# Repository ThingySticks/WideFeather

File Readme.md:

# Wide Feater Wing ThingyStick Prototype PCB

Wide format prototype board for Feather based boards..

## V1

### Features:

* USB power in via A Connector on right hand edge.
* LED/Resistor/Capacitor 1206 pads along top edge, along both top and bottom or board (although you probably don't want both at once!)
* 4 mounting holes (M3 machine screw) to allow board to be mounted in case for final use.
* PCB 100mm x 50mm. Holes at 4mm from edge.

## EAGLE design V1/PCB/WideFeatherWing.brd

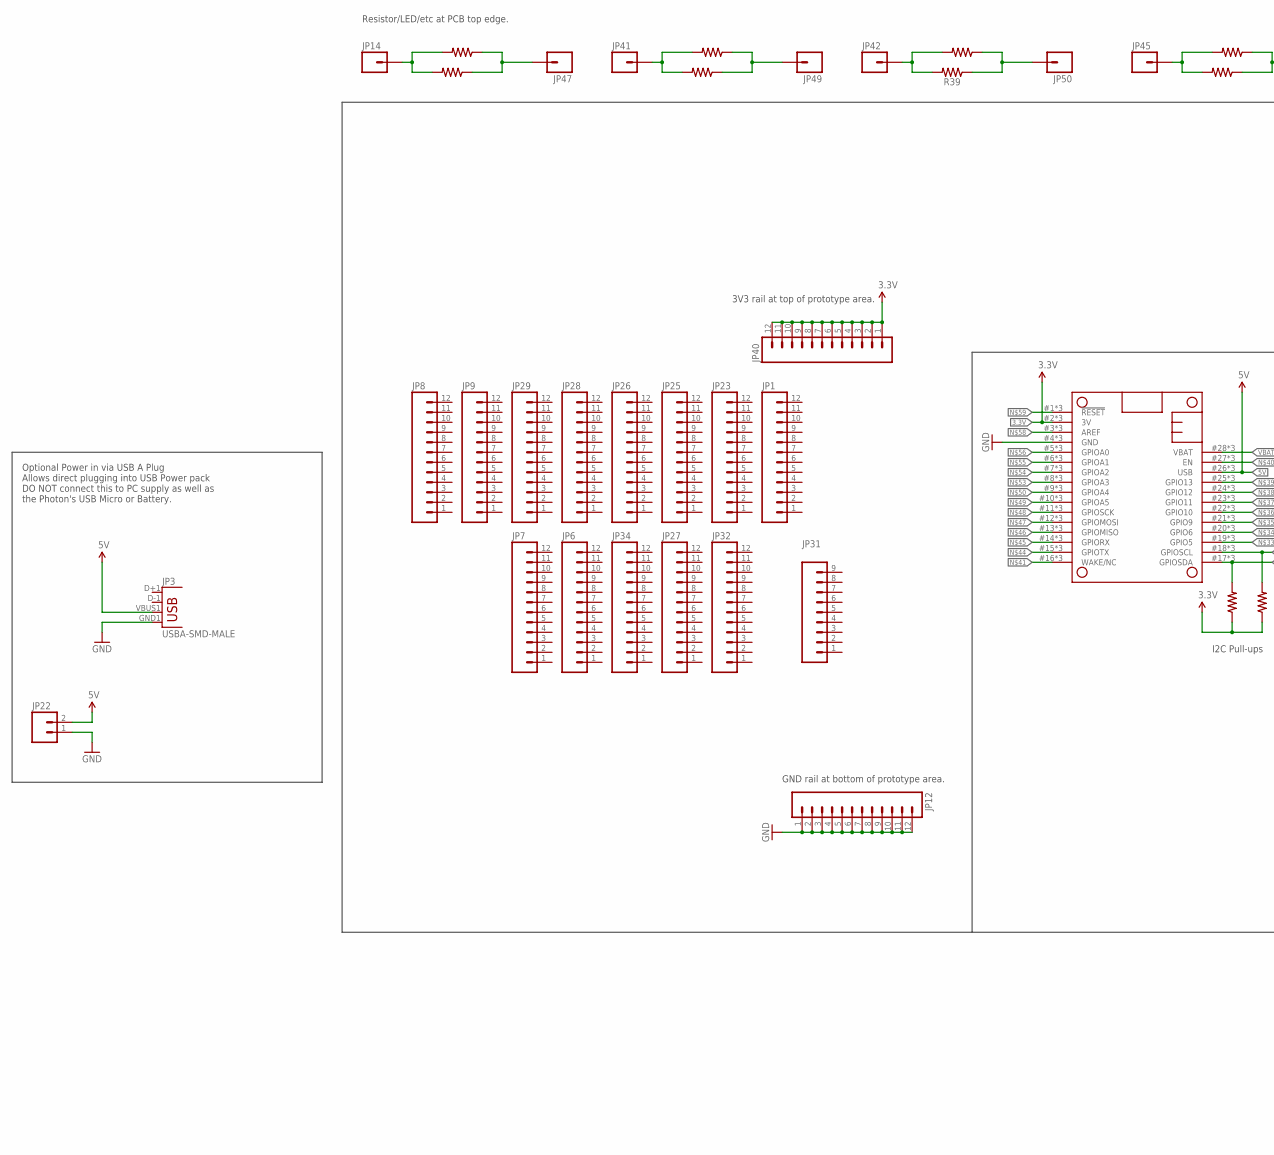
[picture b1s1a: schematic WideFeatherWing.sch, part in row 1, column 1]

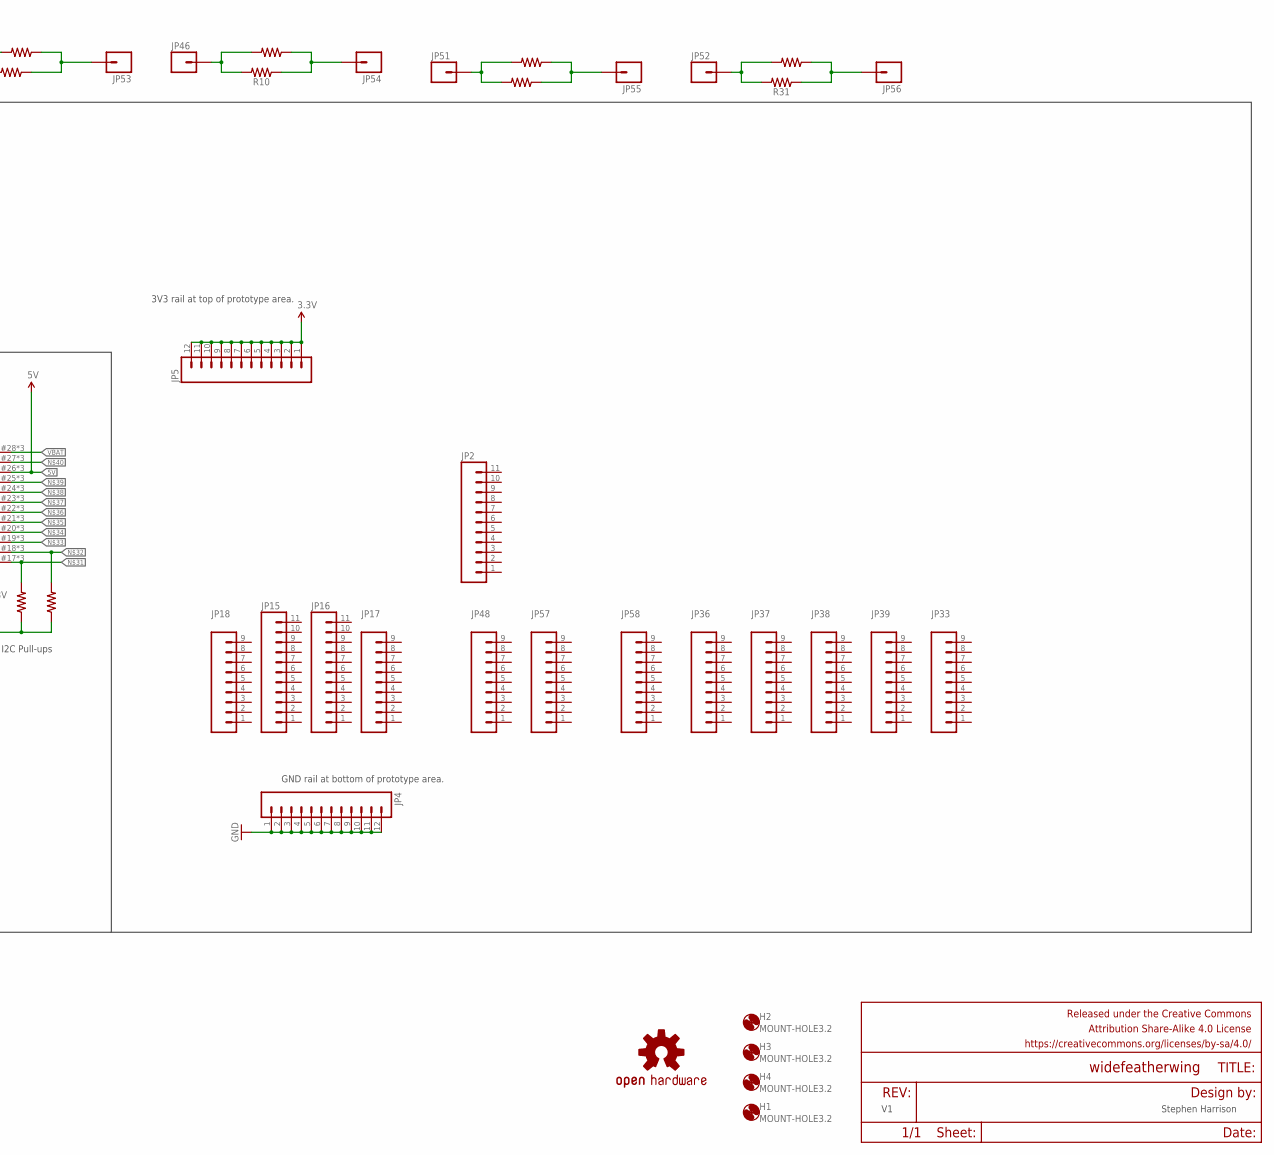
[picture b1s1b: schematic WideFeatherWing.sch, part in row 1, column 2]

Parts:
FRAME1: FRAME-LEDGER; CREATIVE_COMMONS
H1, H2, H3, H4: MOUNT-HOLE3.2; 3,2
JP1, JP6, JP7, JP8, JP9, JP23, JP25, JP26, JP27, JP28, JP29, JP32, JP34: M12NO_SILK; 1X12_NO_SILK
JP2, JP15, JP16: M111X11_NO_SILK; 1X11_NO_SILK
JP3: USBA-SMD-MALE; USB-A-SMT-MALE
JP4, JP5, JP12, JP40: M12PTH; 1X12
JP14, JP41, JP42, JP45, JP46, JP47, JP49, JP50, JP51, JP52, JP53, JP54, JP55, JP56: M01PTH; 1X01
JP17, JP18, JP31, JP33, JP36, JP37, JP38, JP39, JP48, JP57, JP58: M09NO_SILK; 1X09_NO_SILK
JP22: M021X02_NO_SILK; 1X02_NO_SILK
LOGO1: OSHW-LOGOM; OSHW-LOGO-M
MS1: FEATHERWINGFEATHEWING_BREAKOUT; FEATHERWING_BREAKOUT
R5, R9, R10, R17, R24, R30, R31, R32, R34, R35, R36, R37, R39, R40, R41, R44: 1206

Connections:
3.3V: JP5.1, JP5.2, JP5.3, JP5.4, JP5.5, JP5.6, JP5.7, JP5.8, JP5.9, JP5.10, JP5.11, JP5.12, JP40.1, JP40.2, JP40.3, JP40.4, JP40.5, JP40.6, JP40.7, JP40.8, JP40.9, JP40.10, JP40.11, JP40.12, MS1.2 (3V), MS1.#2 (3V), MS1.@2 (3V), R5.1, R9.1
5V: JP3.VBUS1 (VBUS), JP22.2, MS1.26 (USB), MS1.#26 (USB), MS1.@26 (USB)
GND: JP3.GND1 (GND), JP4.1, JP4.2, JP4.3, JP4.4, JP4.5, JP4.6, JP4.7, JP4.8, JP4.9, JP4.10, JP4.11, JP4.12, JP12.1, JP12.2, JP12.3, JP12.4, JP12.5, JP12.6, JP12.7, JP12.8, JP12.9, JP12.10, JP12.11, JP12.12, JP22.1, MS1.4 (GND), MS1.#4 (GND), MS1.@4 (GND)
unnamed: JP42.1, R39.2, R44.2
unnamed: JP53.1, R17.1, R24.1
unnamed: JP45.1, R17.2, R24.2
unnamed: JP46.1, R10.2, R30.2
unnamed: JP54.1, R10.1, R30.1
unnamed: JP55.1, R32.1, R36.1
unnamed: JP51.1, R32.2, R36.2
unnamed: JP56.1, R31.1, R37.1
unnamed: JP52.1, R31.2, R37.2
unnamed: MS1.17 (GPIOSDA), MS1.#17 (GPIOSDA), MS1.@17 (GPIOSDA), R5.2
unnamed: MS1.18 (GPIOSCL), MS1.#18 (GPIOSCL), MS1.@!8 (GPIOSCL), R9.2
unnamed: MS1.19 (GPIO5), MS1.#19 (GPIO5), MS1.@19 (GPIO5)
unnamed: MS1.20 (GPIO6), MS1.#20 (GPIO6), MS1.@20 (GPIO6)
unnamed: MS1.21 (GPIO9), MS1.#21 (GPIO9), MS1.@21 (GPIO9)
unnamed: MS1.22 (GPIO10), MS1.#22 (GPIO10), MS1.@22 (GPIO10)
unnamed: MS1.23 (GPIO11), MS1.#23 (GPIO11), MS1.@23 (GPIO11)
unnamed: MS1.24 (GPIO12), MS1.#24 (GPIO12), MS1.@24 (GPIO12)
unnamed: MS1.25 (GPIO13), MS1.#25 (GPIO13), MS1.@25 (GPIO13)
unnamed: MS1.27 (EN), MS1.#27 (EN), MS1.@27 (EN)
unnamed: MS1.16 (WAKE/NC), MS1.#16 (WAKE/NC), MS1.@16 (WAKE/NC)
unnamed: JP47.1, R34.1, R35.1
unnamed: MS1.15 (GPIOTX), MS1.#15 (GPIOTX), MS1.@15 (GPIOTX)
unnamed: MS1.14 (GPIORX), MS1.#14 (GPIORX), MS1.@14 (GPIORX)
unnamed: MS1.13 (GPIOMISO), MS1.#13 (GPIOMISO), MS1.@13 (GPIOMISO)
unnamed: MS1.12 (GPIOMOSI), MS1.#12 (GPIOMOSI), MS1.@12 (GPIOMOSI)
unnamed: MS1.11 (GPIOSCK), MS1.#11 (GPIOSCK), MS1.@11 (GPIOSCK)
unnamed: MS1.10 (GPIOA5), MS1.#10 (GPIOA5), MS1.@10 (GPIOA5)
unnamed: MS1.9 (GPIOA4), MS1.#9 (GPIOA4), MS1.@9 (GPIOA4)
unnamed: JP14.1, R34.2, R35.2
unnamed: MS1.8 (GPIOA3), MS1.#8 (GPIOA3), MS1.@8 (GPIOA3)
unnamed: MS1.7 (GPIOA2), MS1.#7 (GPIOA2), MS1.@7 (GPIOA2)
unnamed: MS1.6 (GPIOA1), MS1.#6 (GPIOA1), MS1.@6 (GPIOA1)
unnamed: MS1.5 (GPIOA0), MS1.#5 (GPIOA0), MS1.@5 (GPIOA0)
unnamed: MS1.3 (AREF), MS1.#3 (AREF), MS1.@3 (AREF)
unnamed: MS1.1 (!RESET), MS1.#1 (!RESET), MS1.@1 (!RESET)
unnamed: JP49.1, R40.1, R41.1
unnamed: JP41.1, R40.2, R41.2
unnamed: JP50.1, R39.1, R44.1
VBAT: MS1.28 (VBAT), MS1.#28 (VBAT), MS1.@28 (VBAT)

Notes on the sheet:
Resistor/LED/etc at PCB top edge.
Optional Power in via USB A Plug Allows direct plugging into USB Power pack DO NOT connect this to PC supply as well as the Photon's USB Micro or Battery.
GND rail at bottom of prototype area.
3V3 rail at top of prototype area.
I2C Pull-ups
Stephen Harrison

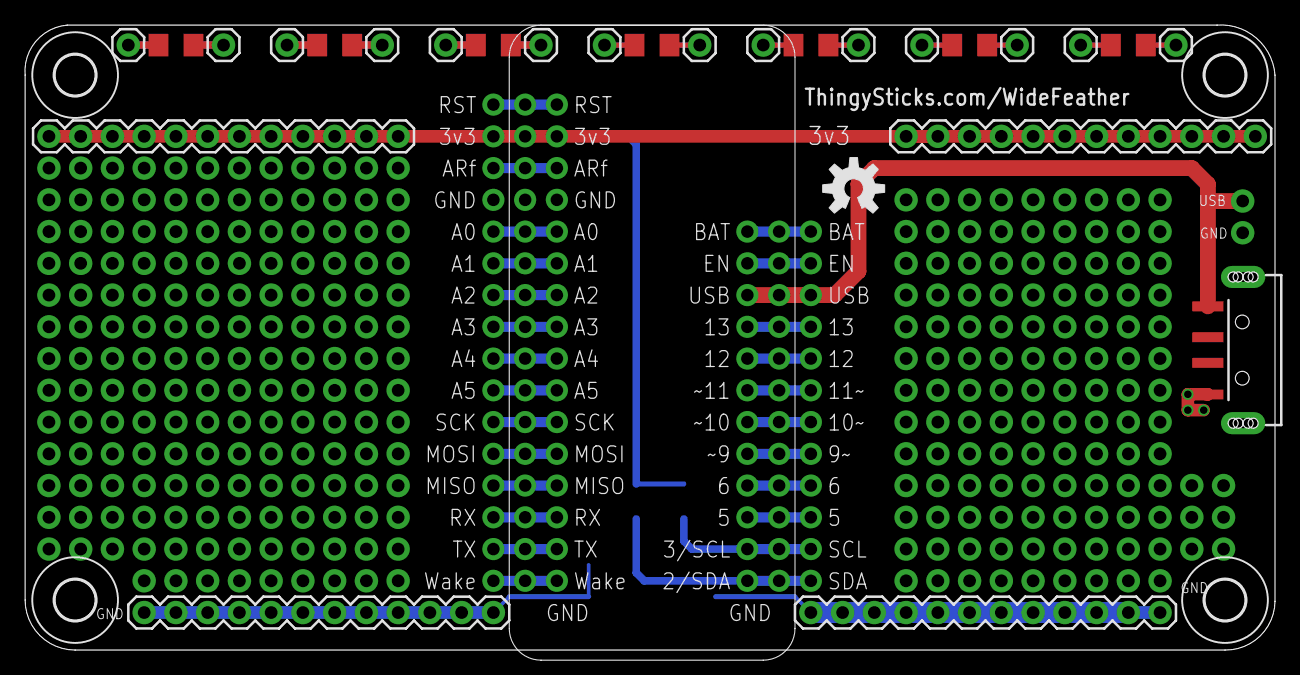
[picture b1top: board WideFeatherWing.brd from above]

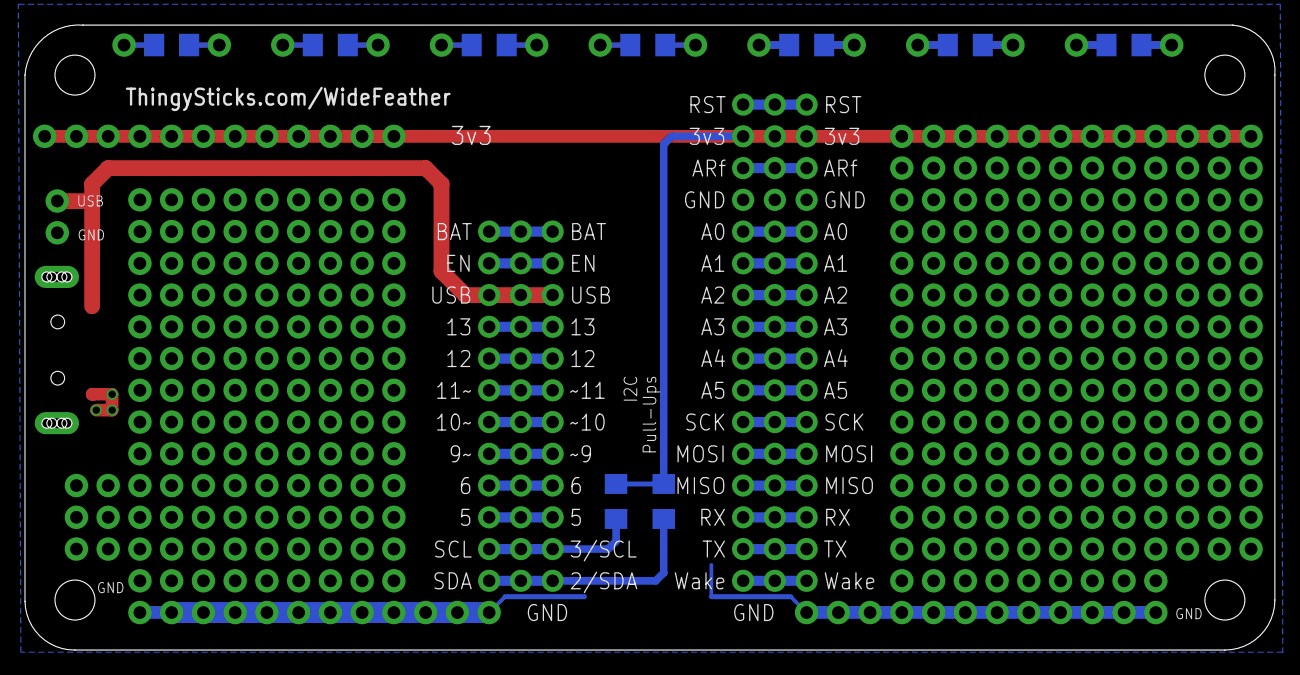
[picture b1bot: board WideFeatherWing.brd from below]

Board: 2 copper layers, 100.0 x 50.0 mm, 70 parts (9 on the bottom side), 42 nets.

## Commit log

2019-01-23 Initial commit.
2019-01-23 Fix markdown mistake.
2019-01-23 Corrected all layers PCB export image filename

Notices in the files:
parts and their libraries:
SparkFun-Connectors: Licensing: Creative Commons ShareAlike 4.0 International - https://creativecommons.org/licenses/by-sa/4.0
SparkFun-Aesthetics: Released under the Creative Commons Attribution Share-Alike 4.0 License
SparkFun-Aesthetics: https://creativecommons.org/licenses/by-sa/4.0
